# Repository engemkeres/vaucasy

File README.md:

# vaucasy
vaucasy is a split, ergonomic mechanical keyboard with a pair of OLEDs, rotary encoders and a trackball. It features a 4x7 staggered ortho layout on both halves.

The MCU chosen for this project was an STM32F401RET6, because I was familiar with STM32s F4 series.

[**QMK firmware**](https://github.com/engemkeres/qmk_firmware/tree/master/keyboards/vaucasy)

**Own firmware** with the support of ST's HAL library: [in progress](https://github.com/engemkeres/vaucasy_firmware)

**JCLPCB order preview:**

Right:

Left:

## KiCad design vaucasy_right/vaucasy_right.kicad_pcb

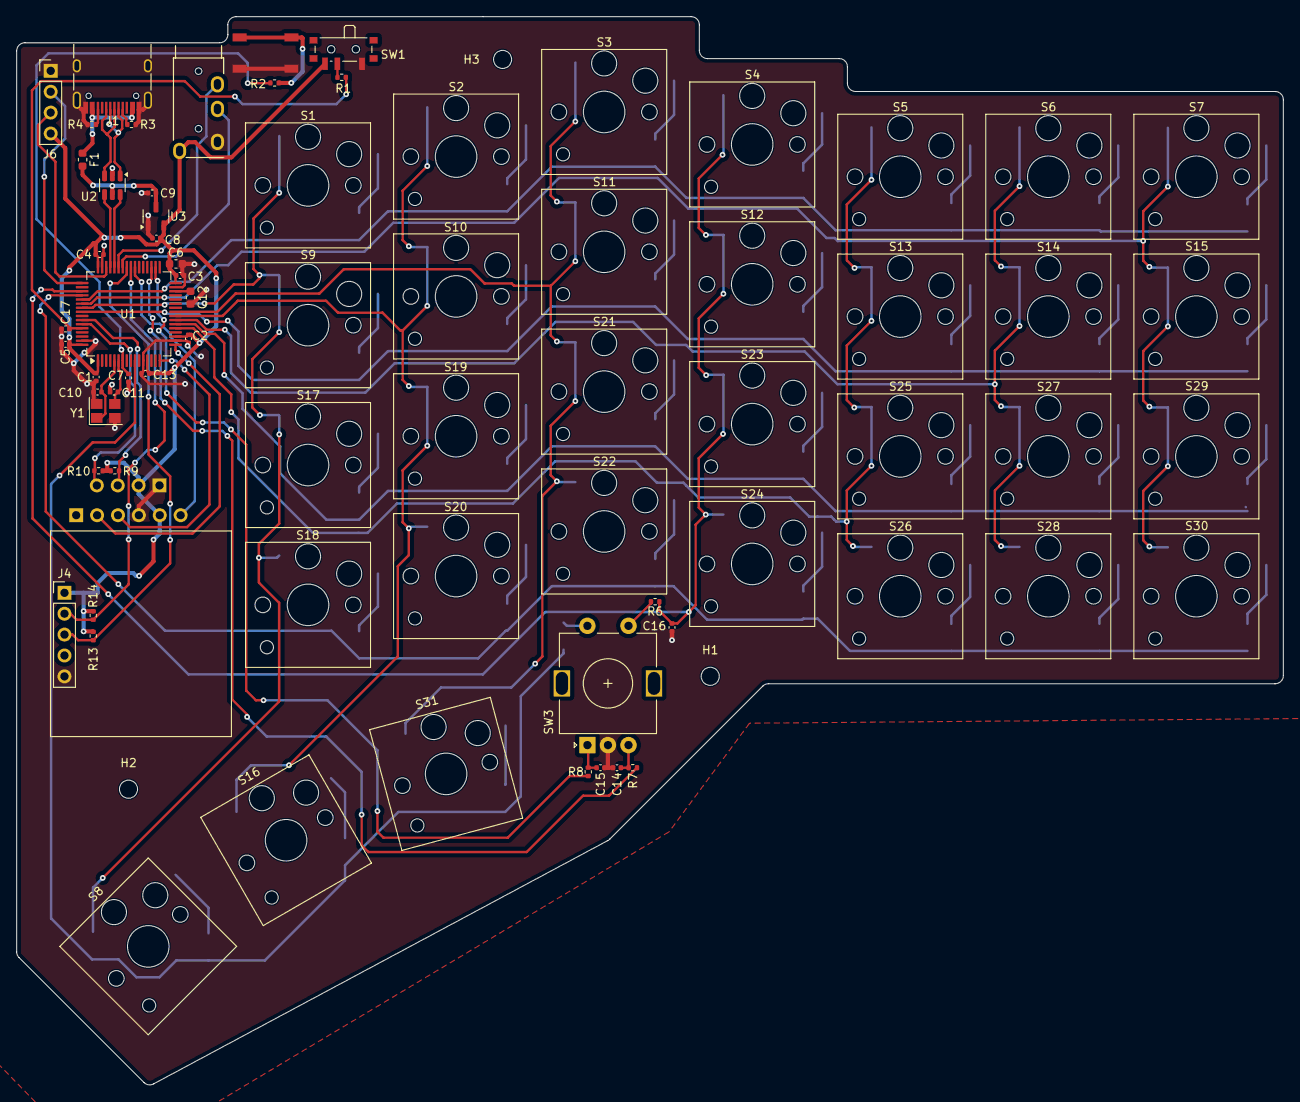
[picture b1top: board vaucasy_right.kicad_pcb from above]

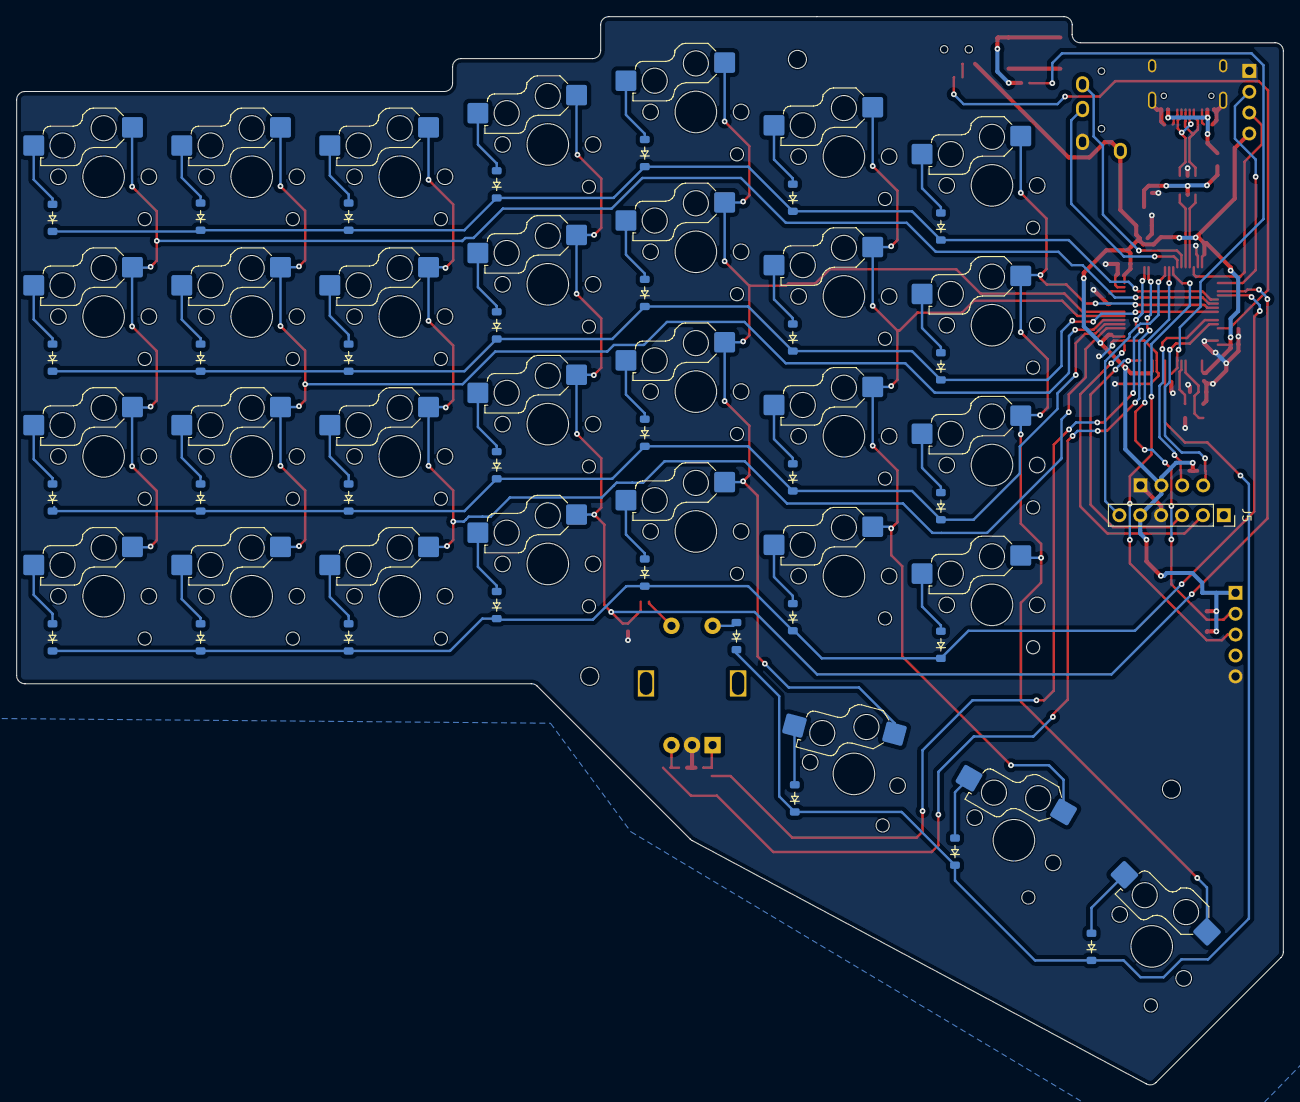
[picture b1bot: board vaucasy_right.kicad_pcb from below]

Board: 2 copper layers, 154.0 x 129.9 mm, 108 parts (33 on the bottom side), 77 nets.

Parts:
C1, C2, C3, C4, C5, C7, C13, C14, C15, C16, C17: 100n; C_0402_1005Metric
C6: 10u; C_0603_1608Metric
C8, C9: 1u; C_0402_1005Metric
C10, C11: 8p; C_0402_1005Metric
C12: 4.7uF; C_0603_1608Metric
D1, D2, D3, D4, D5, D6, D7, D8, D9, D10, D11, D12, D13, D14, D15, D16, D17, D18, D19, D20, D21, D22, D23, D24, D25, D26, D27, D28, D29, D30, D31, D33: Diode; Diode_SOD-123
F1: 500mA; Fuse_0603_1608Metric
H1, H2, H3: MountingHole; MountingHole_2.2mm_M2
J1: USB_C; USB_C_Receptacle_HRO_TYPE-C-31-M-12
J2: OLED_128x32
J4: Trackball; PinHeader_1x05_P2.54mm_Vertical
J5: HC-05 BT; PinSocket_1x06_P2.54mm_Vertical
J6: DEBUG; PinHeader_1x04_P2.54mm_Vertical
R1, R6, R7, R8: 10k; R_0402_1005Metric
R2: 100R; R_0402_1005Metric
R3, R4: 5.1k; R_0402_1005Metric
R9, R10, R13, R14: 4.7k; R_0402_1005Metric
S1, S2, S3, S4, S5, S6, S7, S8, S9, S10, S11, S12, S13, S14, S15, S16, S17, S18, S19, S20, S21, S22, S23, S24, S25, S26, S27, S28, S29, S30, S31: Keyswitch; Hotswap_Choc_V1V2_1.00u
SW1: SW_SPDT; SW_SPDT_PCM12
SW2: SW_Push; Button_TL3342
SW3: RotaryEncoder_Switch; RotaryEncoder_Alps_EC11E-Switch_Vertical_H20mm
U1: STM32F401RET6; LQFP-64_10x10mm_P0.5mm
U2: USBLC6-2SC6; SOT-23-6
U3: XC6206; SOT-23-3
U4: TRRS; TRRS_PJ-320A
Y1: 8MHz; Crystal_SMD_3225-4Pin_3.2x2.5mm

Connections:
+3.3V: C1.2, C2.2, C3.2, C4.2, C5.2, C6.2, C8.2, C13.2, J2.2 (VCC), J4.1 (Vcc), J5.5 (VCC), J6.4, R9.2, R10.1, R13.2, R14.1, SW1.3 (C), U1.1 (VBAT), U1.13 (VREF+), U1.19 (VDD), U1.32 (VDD), U1.48 (VDD), U1.64 (VDD), U3.2 (VO), U4.1 (SLEEVE)
+5V: C9.2, F1.2, U2.5 (VBUS), U3.3 (VI)
/LMCU_VCAP1: C12.1, U1.30 (VCAP1)
/SW_BOOT0: R1.1, SW1.2 (B)
GND: C1.1, C2.1, C3.1, C4.1, C5.1, C6.1, C7.1, C8.1, C9.1, C10.1, C11.1, C12.2, C13.1, C14.1, C15.2, C16.2, C17.2, J1.A1 (GND), J1.A12 (GND), J1.B1 (GND), J1.B12 (GND), J1.S1 (SHIELD), J2.1 (GND), J4.5 (GND), J5.4 (GND), J6.1, R3.1, R4.1, SW1.1 (A), SW2.1, SW3.C, U1.12 (VSSA), U1.18 (VSS), U1.31 (VSS), U1.47 (VSS), U1.63 (VSS), U2.2 (GND), U3.1 (GND), U4.2 (TIP), Y1.2, Y1.4
LBOOT0: C17.1, R1.2, U1.60 (BOOT0)
LBT_EN: J5.6 (EN), U1.39 (PC8)
LColumn 0: S1.1, S8.1, S9.1, S17.1, S18.1, U1.55 (PB3)
LColumn 1: S2.1, S10.1, S16.1, S19.1, S20.1, U1.24 (PC4)
LColumn 2: S3.1, S11.1, S21.1, S22.1, S31.1, U1.25 (PC5)
LColumn 3: C16.1, R6.1, S4.1, S12.1, S23.1, S24.1, U1.51 (PC10)
LColumn 4: S5.1, S13.1, S25.1, S26.1, U1.21 (PA5)
LColumn 5: S6.1, S14.1, S27.1, S28.1, U1.23 (PA7)
LColumn 6: S7.1, S15.1, S29.1, S30.1, U1.54 (PD2)
LD+: J1.A6 (D+), J1.B6 (D+), U2.3 (I/O2)
LD-: J1.A7 (D-), J1.B7 (D-), U2.1 (I/O1)
LENCODER_A: R8.1, U1.34 (PB13)
LENCODER_B: R7.2, U1.35 (PB14)
LNRST: C7.2, R2.1, U1.7 (NRST)
LOLED_SCL: J2.3 (SCL), R9.1, U1.58 (PB6)
LOLED_SDA: J2.4 (SDA), R10.2, U1.59 (PB7)
LOSC_IN: C10.2, U1.5 (PH0), Y1.1
LOSC_OUT: C11.2, U1.6 (PH1), Y1.3
LRow 0: D1.1 (K), D2.1 (K), D3.1 (K), D4.1 (K), D5.1 (K), D6.1 (K), D7.1 (K), U1.53 (PC12)
LRow 1: D9.1 (K), D10.1 (K), D11.1 (K), D12.1 (K), D13.1 (K), D14.1 (K), D15.1 (K), U1.56 (PB4)
LRow 2: D17.1 (K), D19.1 (K), D21.1 (K), D23.1 (K), D25.1 (K), D27.1 (K), D29.1 (K), U1.22 (PA6)
LRow 3: D18.1 (K), D20.1 (K), D22.1 (K), D24.1 (K), D26.1 (K), D28.1 (K), D30.1 (K), U1.52 (PC11)
LRow 4: D8.1 (K), D16.1 (K), D31.1 (K), D33.1 (K), U1.10 (PC2)
LSWCLK: J6.2, U1.49 (PA14)
LSWDIO: J6.3, U1.46 (PA13)
LTRACK_SCL: J4.3 (SCL), R13.1, U1.41 (PA8)
LTRACK_SDA: J4.2 (SDA), R14.2, U1.40 (PC9)
LUART1_RX: U1.43 (PA10), U4.4 (RING2)
LUART1_TX: U1.42 (PA9), U4.3 (RING1)
LUART2_RX: J5.2 (RXD), U1.17 (PA3)
LUART2_TX: J5.3 (TXD), U1.16 (PA2)
LsD+: U1.45 (PA12), U2.4 (I/O2)
LsD-: U1.44 (PA11), U2.6 (I/O1)
unnamed: C14.2, R7.1, SW3.B
unnamed: C15.1, R8.2, SW3.A
unnamed: D1.2 (A), S1.2
unnamed: D2.2 (A), S2.2
unnamed: D3.2 (A), S3.2
unnamed: D4.2 (A), S4.2
unnamed: D5.2 (A), S5.2
unnamed: D6.2 (A), S6.2
unnamed: D7.2 (A), S7.2
unnamed: D8.2 (A), S8.2
unnamed: D9.2 (A), S9.2
unnamed: D10.2 (A), S10.2
unnamed: D11.2 (A), S11.2
unnamed: D12.2 (A), S12.2
unnamed: D13.2 (A), S13.2
unnamed: D14.2 (A), S14.2
unnamed: D15.2 (A), S15.2
unnamed: D16.2 (A), S16.2
unnamed: D17.2 (A), S17.2
unnamed: D18.2 (A), S18.2
unnamed: D19.2 (A), S19.2
unnamed: D20.2 (A), S20.2
unnamed: D21.2 (A), S21.2
unnamed: D22.2 (A), S22.2
unnamed: D23.2 (A), S23.2
unnamed: D24.2 (A), S24.2
unnamed: D25.2 (A), S25.2
unnamed: D26.2 (A), S26.2
unnamed: D27.2 (A), S27.2
unnamed: D28.2 (A), S28.2
unnamed: D29.2 (A), S29.2
unnamed: D30.2 (A), S30.2
unnamed: D31.2 (A), S31.2
unnamed: D33.2 (A), SW3.S2
unnamed: J1.A5 (CC1), R3.2
unnamed: J1.B5 (CC2), R4.2
unnamed: R2.2, SW2.2
unnamed: R6.2, SW3.S1
VBUS: F1.1, J1.A4 (VBUS), J1.A9 (VBUS), J1.B4 (VBUS), J1.B9 (VBUS)

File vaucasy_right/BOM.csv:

Reference,Value,Datasheet,Footprint,Qty,DNP,JLCPCB part#
"C1,C2,C3,C4,C5,C7,C13,C14,C15,C16,C17",100n,~,Capacitor_SMD:C_0402_1005Metric,11,,C1525
C6,10u,~,Capacitor_SMD:C_0603_1608Metric,1,,C19702
"C8,C9",1u,~,Capacitor_SMD:C_0402_1005Metric,2,,C52923
"C10,C11",8p,~,Capacitor_SMD:C_0402_1005Metric,2,,C1578
C12,4.7uF,~,Capacitor_SMD:C_0603_1608Metric,1,,C19666
"D1,D2,D3,D4,D5,D6,D7,D8,D9,D10,D11,D12,D13,D14,D15,D16,D17,D18,D19,D20,D21,D22,D23,D24,D25,D26,D27,D28,D29,D30,D31,D33",Diode,,ScottoKeebs_Components:Diode_SOD-123,32,,C7420318
F1,500mA,~,Fuse:Fuse_0603_1608Metric,1,,C210357
J1,USB_C,https://www.usb.org/sites/default/files/documents/usb_type-c.zip,Connector_USB:USB_C_Receptacle_HRO_TYPE-C-31-M-12,1,,C165948
J2,OLED_128x32,,ScottoKeebs_Components:OLED_128x32,1,,C5248081
J4,Trackball,~,Connector_PinHeader_2.54mm:PinHeader_1x05_P2.54mm_Vertical,1,,
J5,HC-05 BT,~,Connector_PinSocket_2.54mm:PinSocket_1x06_P2.54mm_Vertical,1,,
J6,DEBUG,~,Connector_PinHeader_2.54mm:PinHeader_1x04_P2.54mm_Vertical,1,,
"R1,R6,R7,R8",10k,~,Resistor_SMD:R_0402_1005Metric,4,,C25744
R2,100R,~,Resistor_SMD:R_0402_1005Metric,1,,C25076
"R3,R4",5.1k,~,Resistor_SMD:R_0402_1005Metric,2,,C25905
"R9,R10,R13,R14",4.7k,~,Resistor_SMD:R_0402_1005Metric,4,,C25900
"S1,S2,S3,S4,S5,S6,S7,S8,S9,S10,S11,S12,S13,S14,S15,S16,S17,S18,S19,S20,S21,S22,S23,S24,S25,S26,S27,S28,S29,S30,S31",Keyswitch,~,ScottoKeebs_Hotswap:Hotswap_Choc_V1V2_1.00u,31,,
SW1,SW_SPDT,~,Button_Switch_SMD:SW_SPDT_PCM12,1,,C221841
SW2,SW_Push,~,ScottoKeebs_Components:Button_TL3342,1,,C115351
SW3,RotaryEncoder_Switch,~,Rotary_Encoder:RotaryEncoder_Alps_EC11E-Switch_Vertical_H20mm,1,,C470788
U1,STM32F401RET6,https://www.st.com/resource/en/datasheet/stm32f401re.pdf,Package_QFP:LQFP-64_10x10mm_P0.5mm,1,,C116978
U2,USBLC6-2SC6,https://www.st.com/resource/en/datasheet/usblc6-2.pdf,Package_TO_SOT_SMD:SOT-23-6,1,,C2827654
U3,XC6206,https://www.torexsemi.com/file/xc6206/XC6206.pdf,Package_TO_SOT_SMD:SOT-23-3,1,,C5446
U4,TRRS,,ScottoKeebs_Components:TRRS_PJ-320A,1,,C22459514
Y1,8MHz,~,Crystal:Crystal_SMD_3225-4Pin_3.2x2.5mm,1,,C7275083

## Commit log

2024-09-14 Initialize project
2024-09-14 Add submodules
2024-09-14 Added ScottoKicad library
    Couldn't add as a submodule
2024-09-14 Set up libraries
2024-09-14 Added MCU
2024-09-16 Switch matrix, connector and OLED added
2024-09-28 Schematic finished
2024-09-28 Started PCB layout
2024-10-03 Left side finished
2024-10-07 Track_INT added
2024-10-07 DIrectory restructure
2024-11-04 ordered
2024-11-11 Update README.md with pictures
2024-12-10 Bill of Materials
    JLCPCB order numbers
